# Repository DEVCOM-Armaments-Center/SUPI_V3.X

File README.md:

# Small Universal Payload Interface (sUPI)

**Technical Data Package, Version 3.3**

> **DISTRIBUTION STATEMENT A. APPROVED FOR PUBLIC RELEASE; DISTRIBUTION IS UNLIMITED.**

sUPI connects one payload to one uncrewed platform. The platform is usually a small UAS. The sUPI
has two halves that latch together. Nine spring-pin contacts connect the halves. These contacts
carry battery power, USB, two 3.3 V PWM lines and a payload-detect line.

sUPI was developed for U.S. Army Special Operations Command. DEVCOM Armaments Center curates the
technical data package. CLIK Lite in Appendix A of the Picatinny Common Lethality Integration Kit
(CLIK) Design Standard uses the sUPI design as its model. CLIK Lite is for platforms that have limits on
size, weight and power, for example Short Range Reconnaissance and Purpose Built Attritable System
aircraft. The full CLIK rail and network interface is too large for these platforms.

| Half | Attaches to | Function |
| --- | --- | --- |
| Platform side | The vehicle | Controls and monitors the payload power, switches the USB, and holds the interface MCU |
| Payload side | The payload | Changes the platform battery voltage to the payload voltages, and holds the payload ID device |

## Repository contents

| Folder | Contents |
| --- | --- |
| [`Documentation/`](Documentation) | Integration briefs, electrical and mechanical references, conventions, change log, manufacturing notes |
| [`Documentation/Known Issues/`](Documentation/Known%20Issues) | Open errata, one file for each issue |
| [`sUPI Electrical/`](sUPI%20Electrical) | KiCad projects for the platform card and the payload card, with schematics, fabrication drawings, Gerber and drill data, stencil data, BOMs and pick-and-place files |
| [`sUPI Mechanicals/`](sUPI%20Mechanicals) | Released drawings and STEP models for assembly `13122513` and its five parts |
| [`sUPI Firmware/`](sUPI%20Firmware) | Platform MCU firmware source, Keil and CubeMX projects, and a built `.hex` file |

The KiCad projects and the released drawings are the golden source. If a document does not agree
with them, use the design data.

## Where to start

| If you | Read these documents in this order |
| --- | --- |
| Install the platform side | [Platform brief](Documentation/sUPI_Platform_Brief.md), assembly drawing, platform schematic |
| Install the payload side | [Payload brief](Documentation/sUPI_Payload_Brief.md), assembly drawing, payload schematic |
| Make the boards | [Known Issues](Documentation/Known%20Issues/README.md), `MFR_*.md` notes, [Electrical Reference](Documentation/Electrical_Reference.md), fabrication drawing, BOM and pick-and-place file |
| Machine the parts | [Known Issues](Documentation/Known%20Issues/README.md), [Mechanical Reference](Documentation/Mechanical_Reference.md), detail drawing and its STEP model |
| Work on the firmware | [Firmware README](sUPI%20Firmware/README.md), MCU sheet of the platform schematic, `Core/Src/supi.c` |
| Make a payload for sUPI | CLIK Design Standard, Appendix A (get it from the design activity), payload brief |

## Before you make boards

Five [known issues](Documentation/Known%20Issues/README.md) have an effect on the order and the
assembly of the boards. Three manufacturing notes change the BOMs:

- [`MFR_DNP.md`](Documentation/MFR_DNP.md): Do not install platform `U3`, `R1` to `R4`, `C2` and
  `JP1`. The undervoltage cutoff is not complete. It can stop the power to the payload.
- [`MFR_Rework.md`](Documentation/MFR_Rework.md): Remove platform `U11` and `U12`. Then connect
  pin 2 to pin 4 on each footprint. If you only remove the parts, the net stays open.
- [`MFR_Capacitors.md`](Documentation/MFR_Capacitors.md): Use the non-Murata alternative parts. The
  released BOMs still show the Murata part numbers.

The platform BOM and pick-and-place file still show all the parts that the first two notes remove.
Use the two notes with the BOM. Where they do not agree with the BOM, obey the notes.

## Version 3.3

On the mechanical side, v3.3 makes the parts easier to machine and makes the fit better. The
machining plan does not need special tools. The parts that mate have less play between them. On the
electrical side, v3.3 contains the KiCad reference design for the two cards and the platform
firmware source. Each v3.3 part has its version number engraved on it. Examine this number before
you mate halves from different versions. Refer to the [change log](Documentation/CHANGELOG.md).

## Contributions and license

sUPI is a reference design. It will change over time. To tell us about a problem or to send a
change, use GitHub issues and pull requests. Refer to [`CONTRIBUTING.md`](CONTRIBUTING.md). The
CERN Open Hardware Licence v2, Weakly Reciprocal, applies to the design ([`LICENSE.md`](LICENSE.md)).

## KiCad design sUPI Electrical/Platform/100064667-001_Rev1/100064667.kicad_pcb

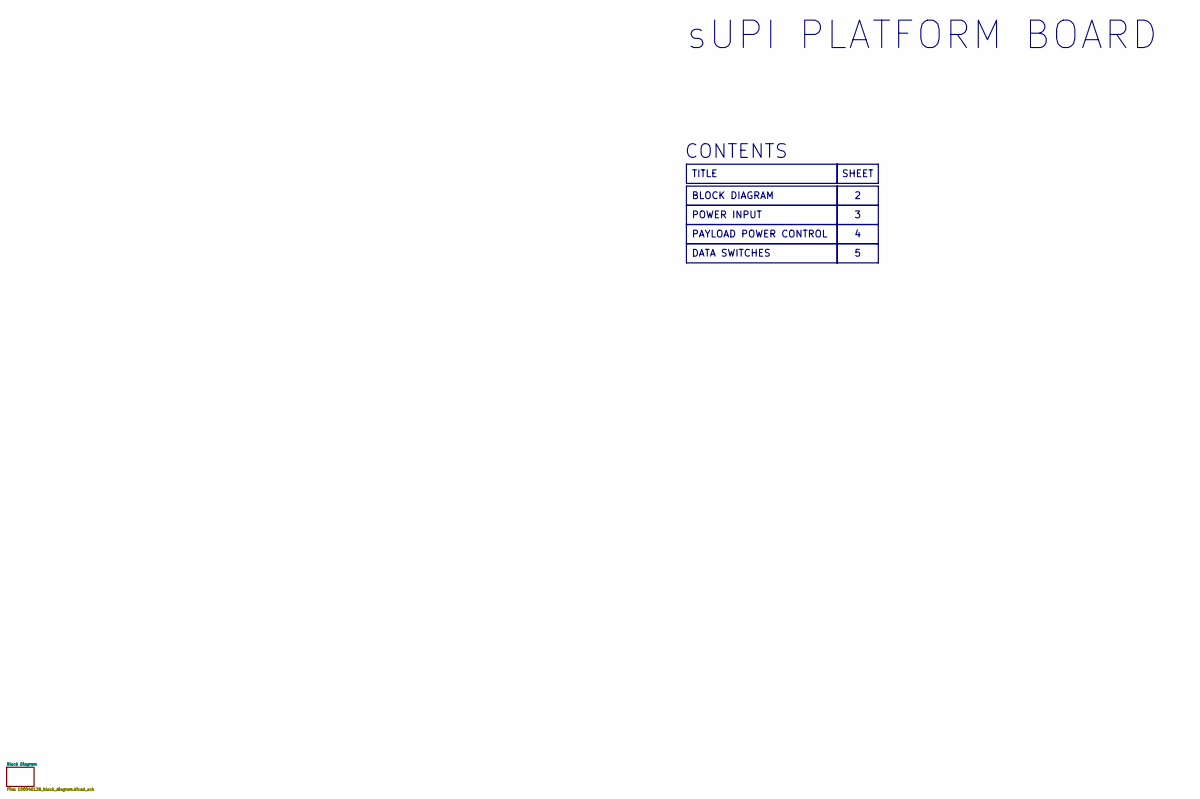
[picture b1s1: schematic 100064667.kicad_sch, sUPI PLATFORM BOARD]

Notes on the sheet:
DATA SWITCHES
PAYLOAD POWER CONTROL
BLOCK DIAGRAM
TITLE
POWER INPUT
SHEET
sUPI PLATFORM BOARD
CONTENTS

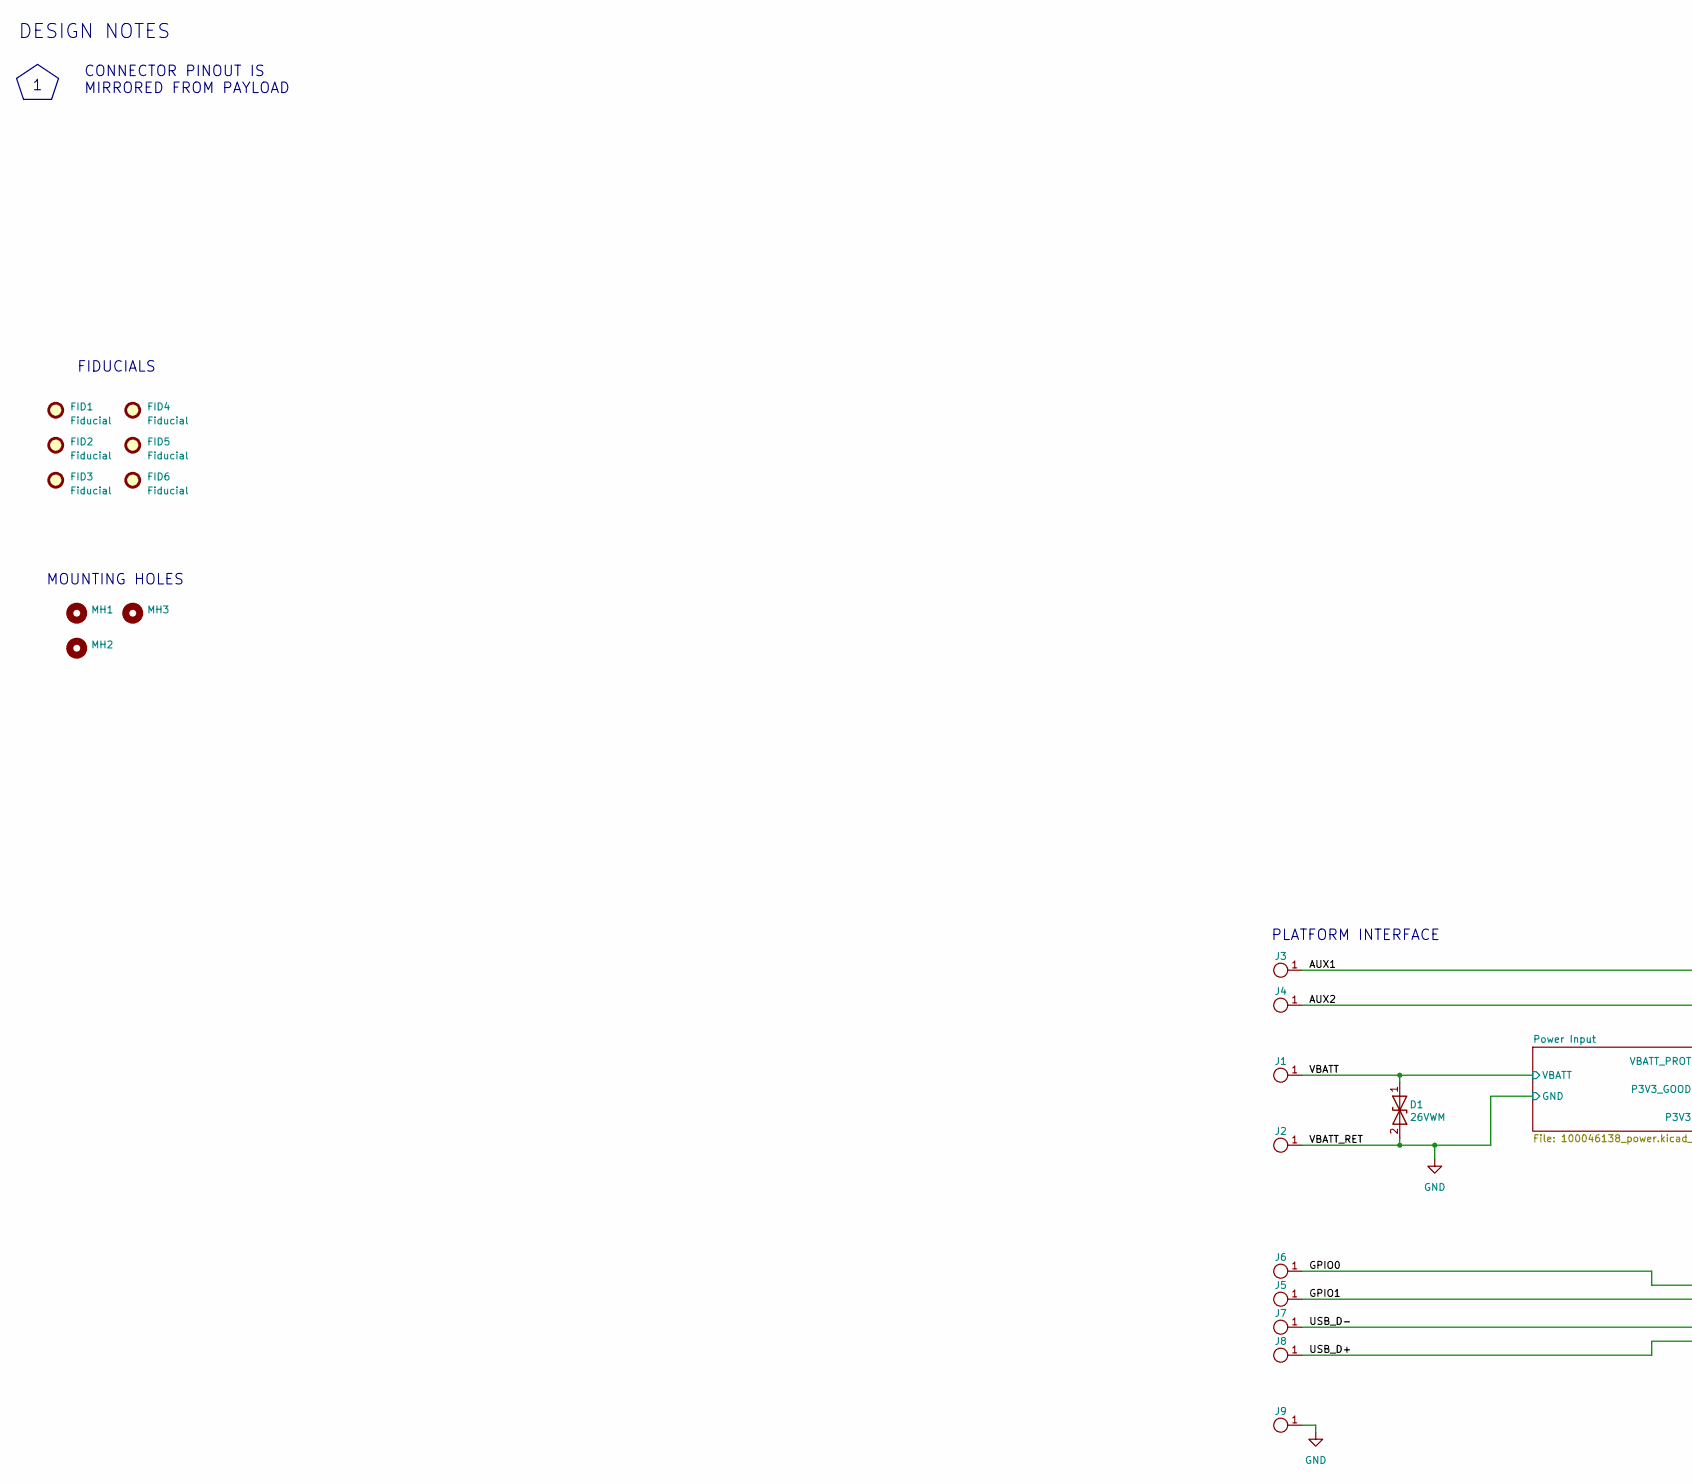
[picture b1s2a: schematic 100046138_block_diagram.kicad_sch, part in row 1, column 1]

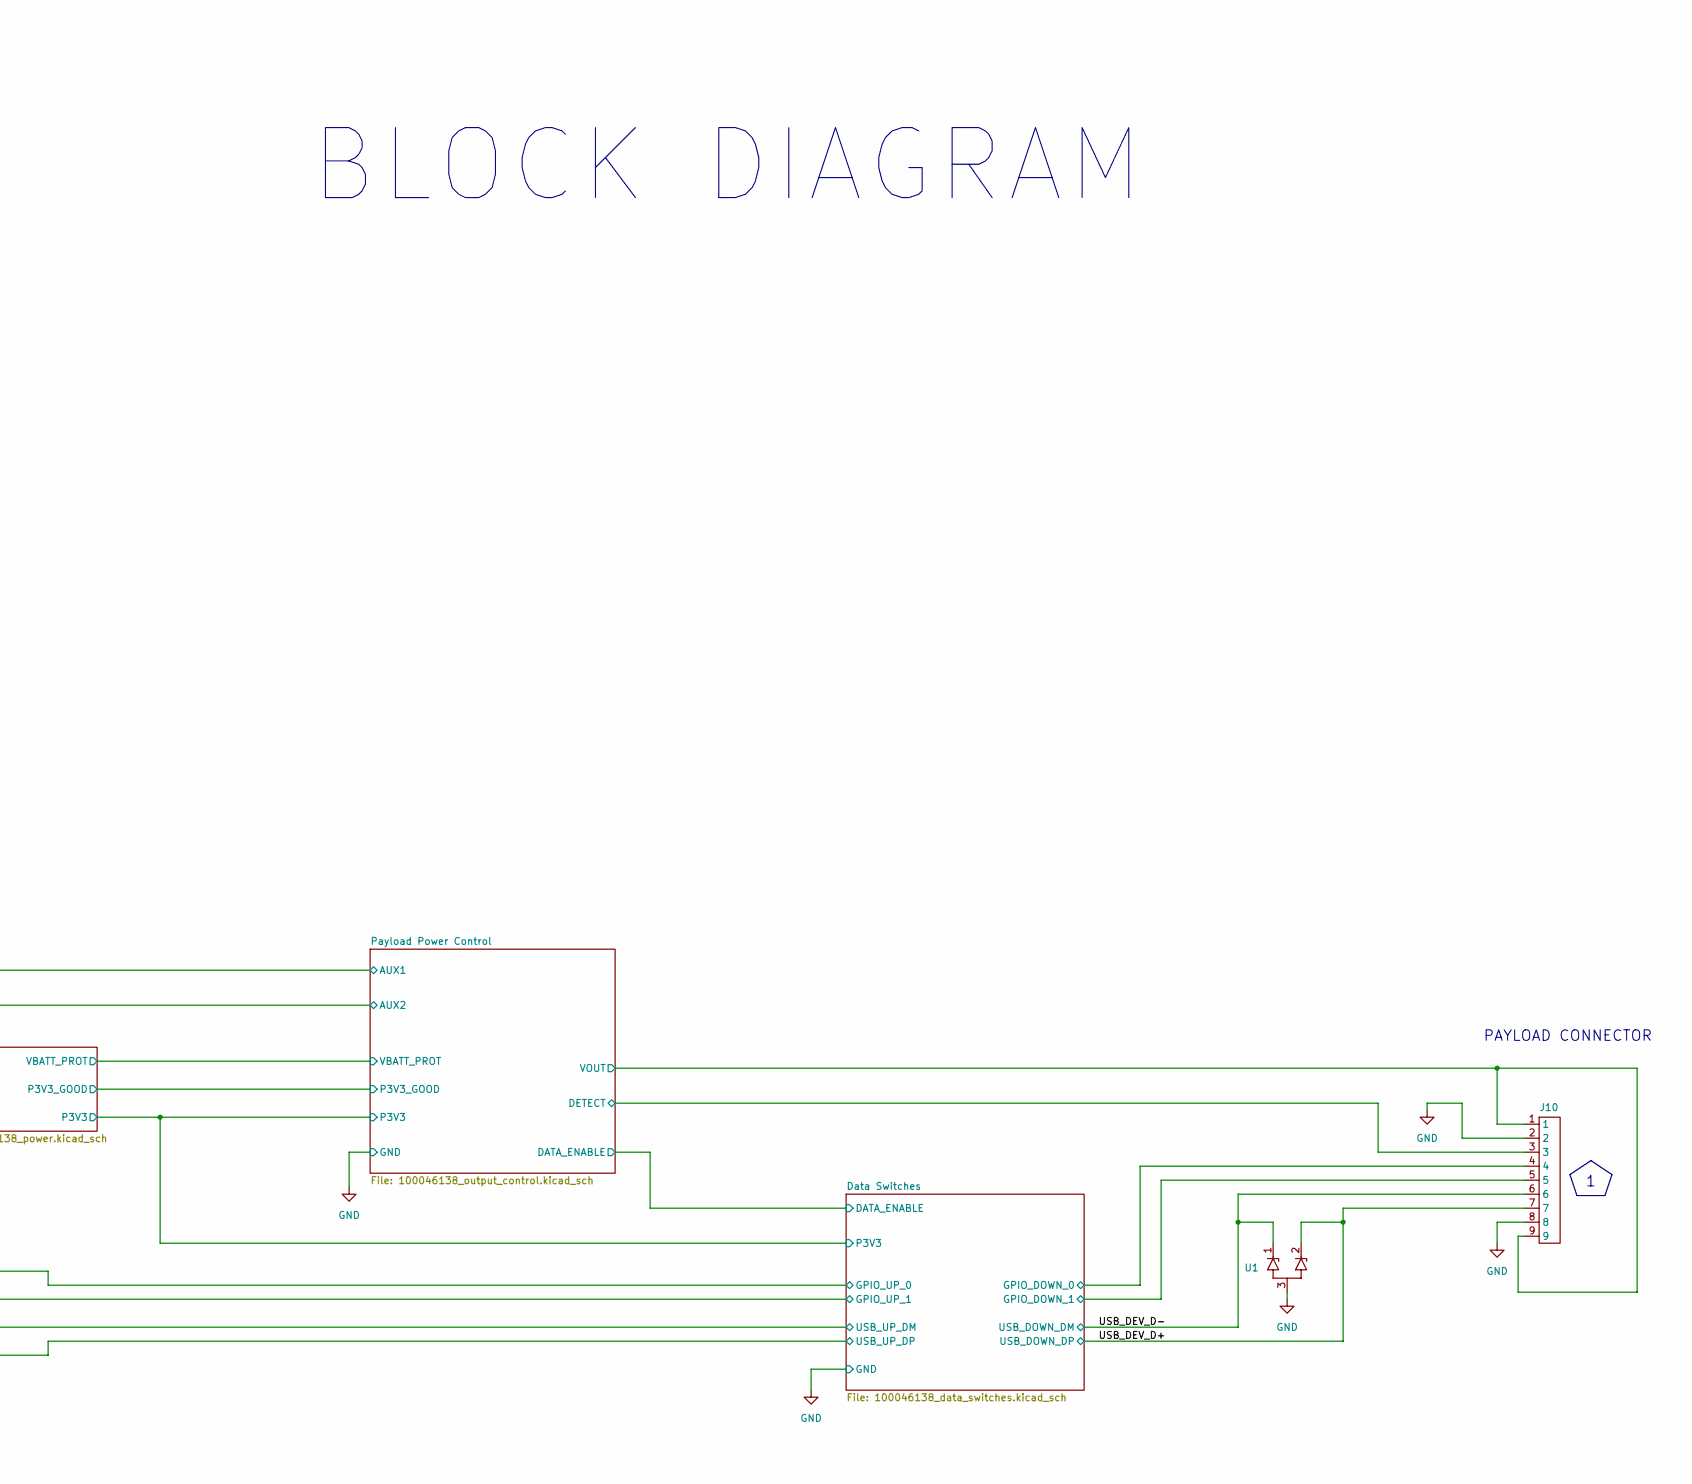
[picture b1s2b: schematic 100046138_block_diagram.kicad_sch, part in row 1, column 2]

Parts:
D1: 26VWM; SOD-123FL; MPN SMF26CA
FID1, FID2, FID3, FID4, FID5, FID6: Fiducial; Fiducial_Cu0.040_Mask0.060
J1, J2: PTH_18AWG
J3, J4, J5, J6, J7, J8, J9: PTH_24AWG_offset_rectangular
J10: 399-10-109-10-007000; MPN 399-10-109-10-007000
MH1, MH2, MH3: 96773A622_M1.6_screw_hole_0.125in_keepout
U1: Diodes_DFN1006-3; MPN PESD5V0C2UM

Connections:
/Block Diagram/AUX1: J3.1; also elsewhere on the board
/Block Diagram/AUX2: J4.1; also elsewhere on the board
/Block Diagram/Data Switches/GPIO_DOWN_0: J10.4; also elsewhere on the board
/Block Diagram/Data Switches/GPIO_DOWN_1: J10.5; also elsewhere on the board
/Block Diagram/GPIO0: J6.1; also elsewhere on the board
/Block Diagram/GPIO1: J5.1; also elsewhere on the board
/Block Diagram/Payload Power Control/DETECT: J10.3; also elsewhere on the board
/Block Diagram/Payload Power Control/VOUT: J10.1, J10.9; also elsewhere on the board
/Block Diagram/USB_D+: J8.1; also elsewhere on the board
/Block Diagram/USB_D-: J7.1; also elsewhere on the board
/Block Diagram/USB_DEV_D+: J10.7, U1.2 (K2); also elsewhere on the board
/Block Diagram/USB_DEV_D-: J10.6, U1.1 (K1); also elsewhere on the board
/Block Diagram/VBATT: D1.1 (A1), J1.1; also elsewhere on the board
GND: D1.2 (A2), J2.1, J9.1, J10.2, J10.8, U1.3 (A); also elsewhere on the board

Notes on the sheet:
MOUNTING HOLES
BLOCK DIAGRAM
DESIGN NOTES
PAYLOAD CONNECTOR
FIDUCIALS
CONNECTOR PINOUT IS MIRRORED FROM PAYLOAD
PLATFORM INTERFACE

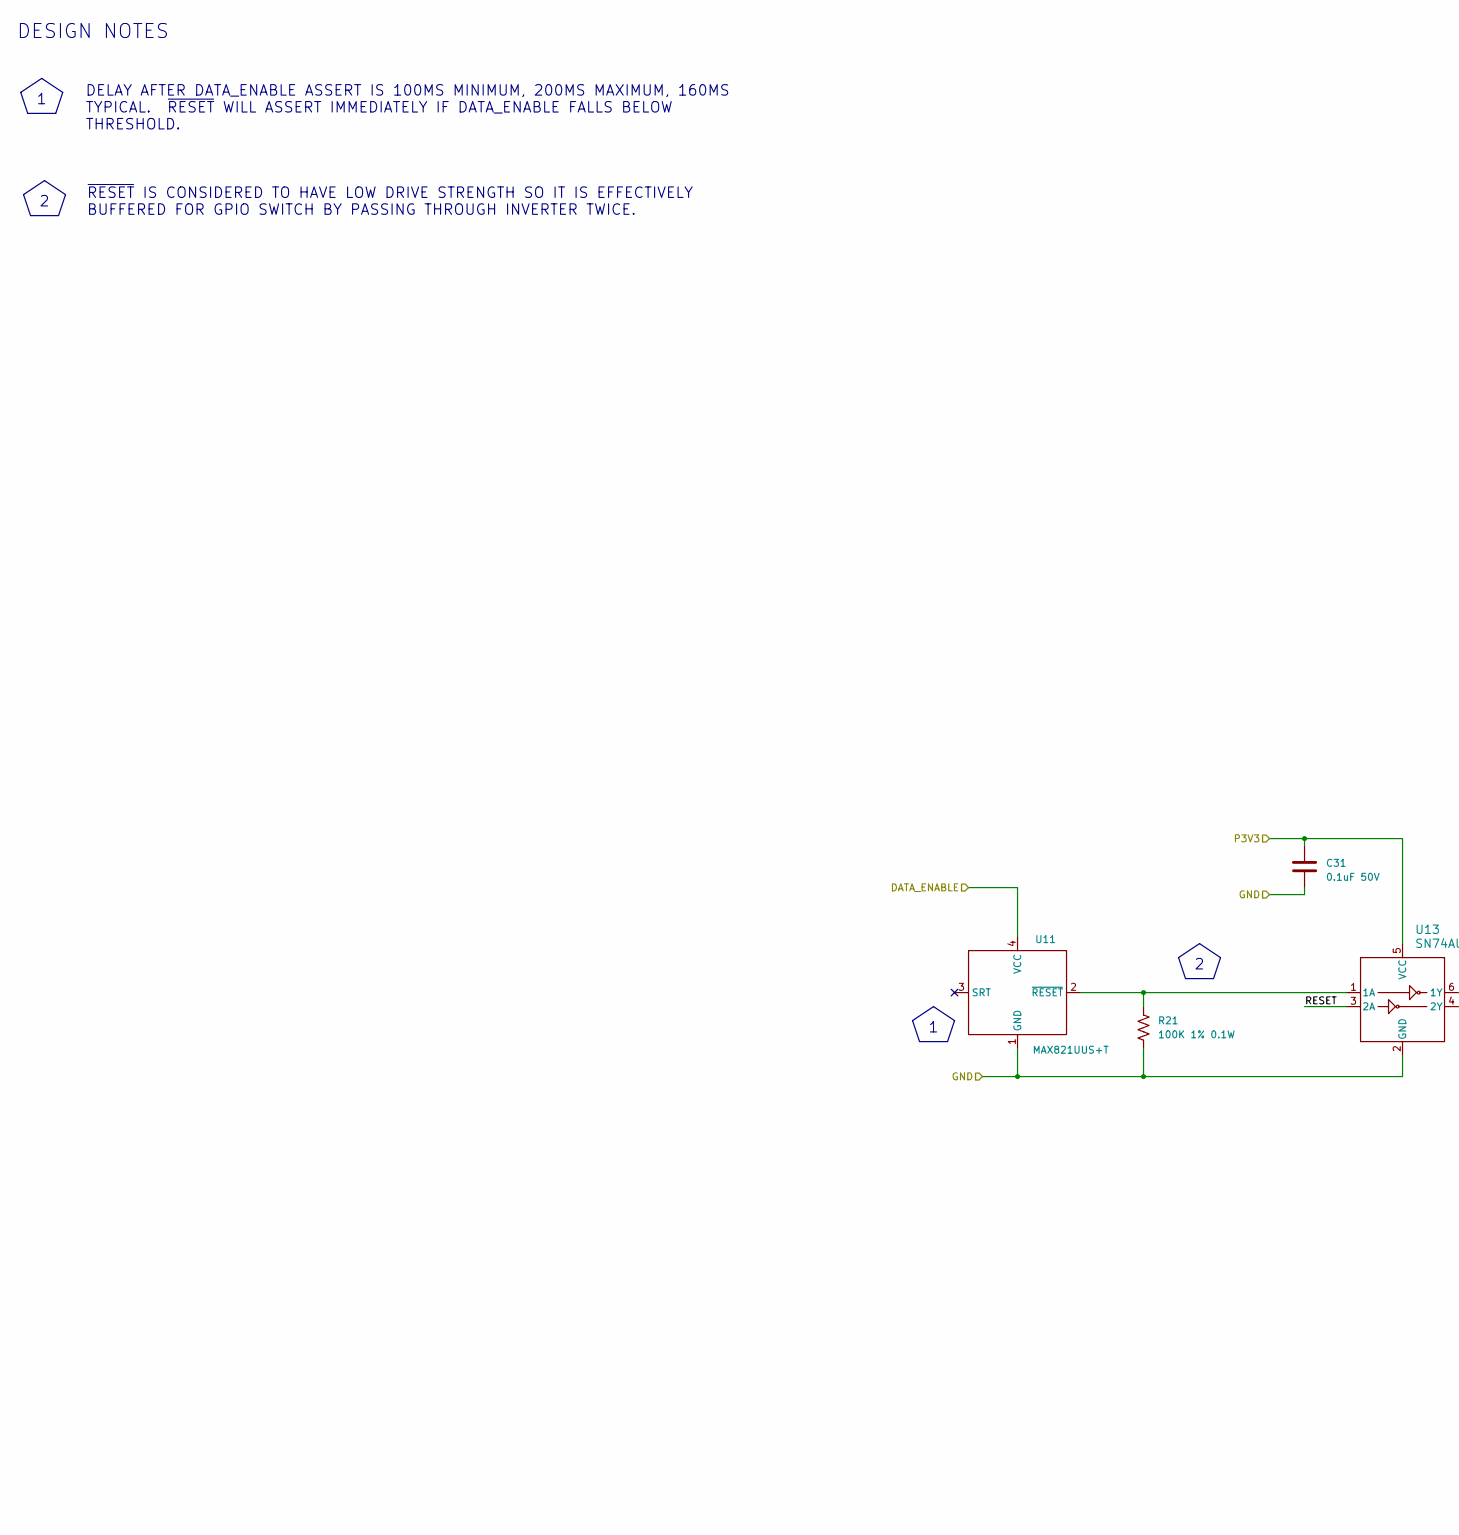
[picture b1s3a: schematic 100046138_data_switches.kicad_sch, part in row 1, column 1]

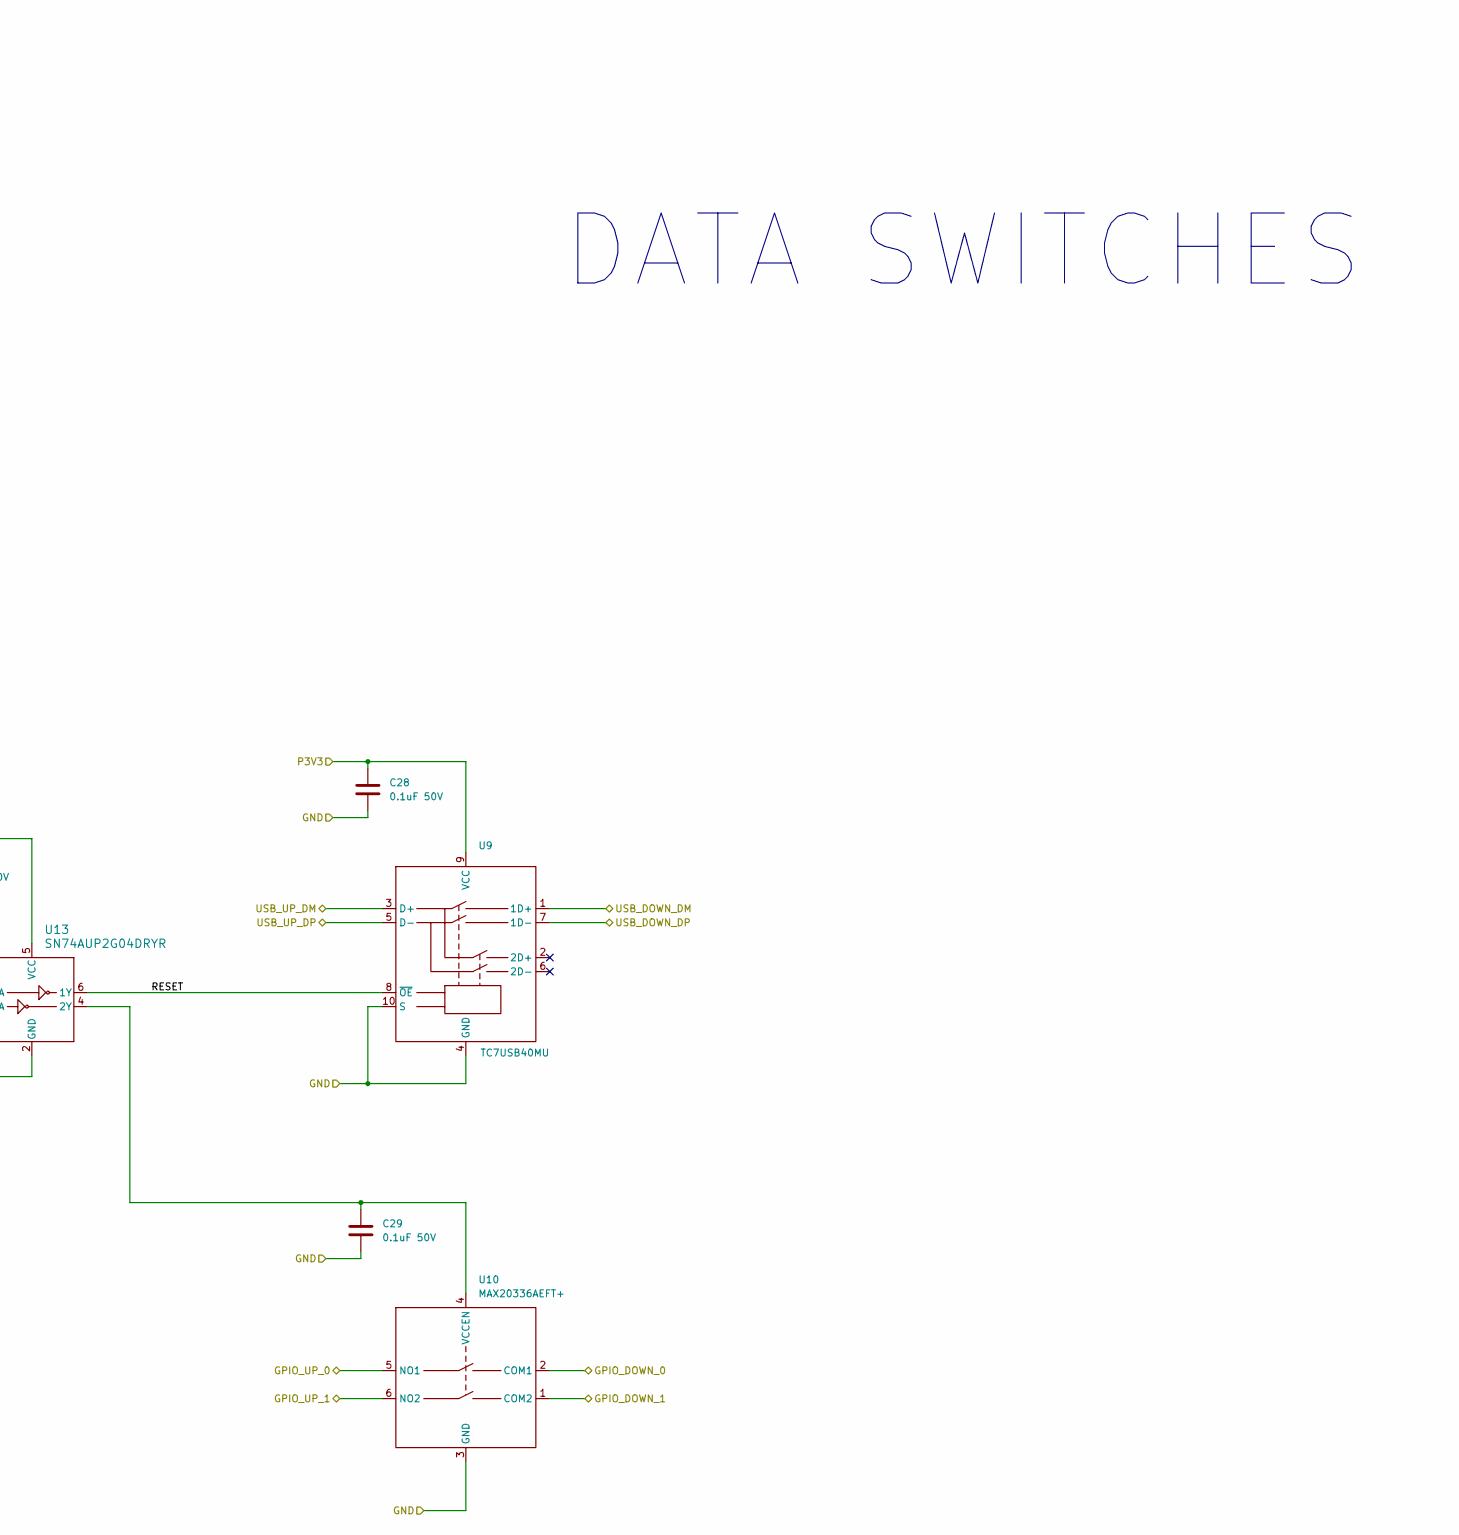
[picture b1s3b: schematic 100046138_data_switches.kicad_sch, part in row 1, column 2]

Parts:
C28, C29, C31: 0.1uF 50V; C_0402_1005Metric; MPN GCM155R71H104ME02D
R21: 100K 1% 0.1W; R_0402_1005Metric; MPN ERJ-2RKF1003X
U9: Toshiba UQFN-10_1.4x1.8mm_P0.4mm; MPN TC7USB40MU
U10: FC2QFN-6; MPN MAX20336AEFT+
U11: SOT-143 Maxim; MPN MAX821UUS+T
U13: SN74AUP2G04DRYR; QFN-6_1.4x1mm_P0.5mm TI DRY6; MPN SN74AUP3G04DQER

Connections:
/Block Diagram/Data Switches/DATA_ENABLE: U11.4 (VCC); also elsewhere on the board
/Block Diagram/Data Switches/GPIO_DOWN_0: U10.2 (COM1); also elsewhere on the board
/Block Diagram/Data Switches/GPIO_DOWN_1: U10.1 (COM2); also elsewhere on the board
/Block Diagram/Data Switches/P3V3: C28.1, C31.1, U9.9 (VCC), U13.5 (VCC); also elsewhere on the board
/Block Diagram/Data Switches/RESET: U9.8 (~OE), U13.3 (2A), U13.6 (1Y)
/Block Diagram/GPIO0: U10.5 (NO1); also elsewhere on the board
/Block Diagram/GPIO1: U10.6 (NO2); also elsewhere on the board
/Block Diagram/USB_D+: U9.5 (D-); also elsewhere on the board
/Block Diagram/USB_D-: U9.3 (D+); also elsewhere on the board
/Block Diagram/USB_DEV_D+: U9.7 (1D-); also elsewhere on the board
/Block Diagram/USB_DEV_D-: U9.1 (1D+); also elsewhere on the board
GND: C28.2, C29.2, C31.2, R21.2, U9.4 (GND), U9.10 (S), U10.3 (GND), U11.1 (GND), U13.2 (GND); also elsewhere on the board
unnamed: C29.1, U10.4 (VCCEN), U13.4 (2Y)
unnamed: R21.1, U11.2 (~RESET), U13.1 (1A)

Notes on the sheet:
DESIGN NOTES
DATA SWITCHES
DELAY AFTER DATA_ENABLE ASSERT IS 100MS MINIMUM, 200MS MAXIMUM, 160MS TYPICAL. ~{RESET} WILL ASSERT IMMEDIATELY IF DATA_ENABLE FALLS BELOW THRESHOLD.
~{RESET} IS CONSIDERED TO HAVE LOW DRIVE STRENGTH SO IT IS EFFECTIVELY BUFFERED FOR GPIO SWITCH BY PASSING THROUGH INVERTER TWICE.
